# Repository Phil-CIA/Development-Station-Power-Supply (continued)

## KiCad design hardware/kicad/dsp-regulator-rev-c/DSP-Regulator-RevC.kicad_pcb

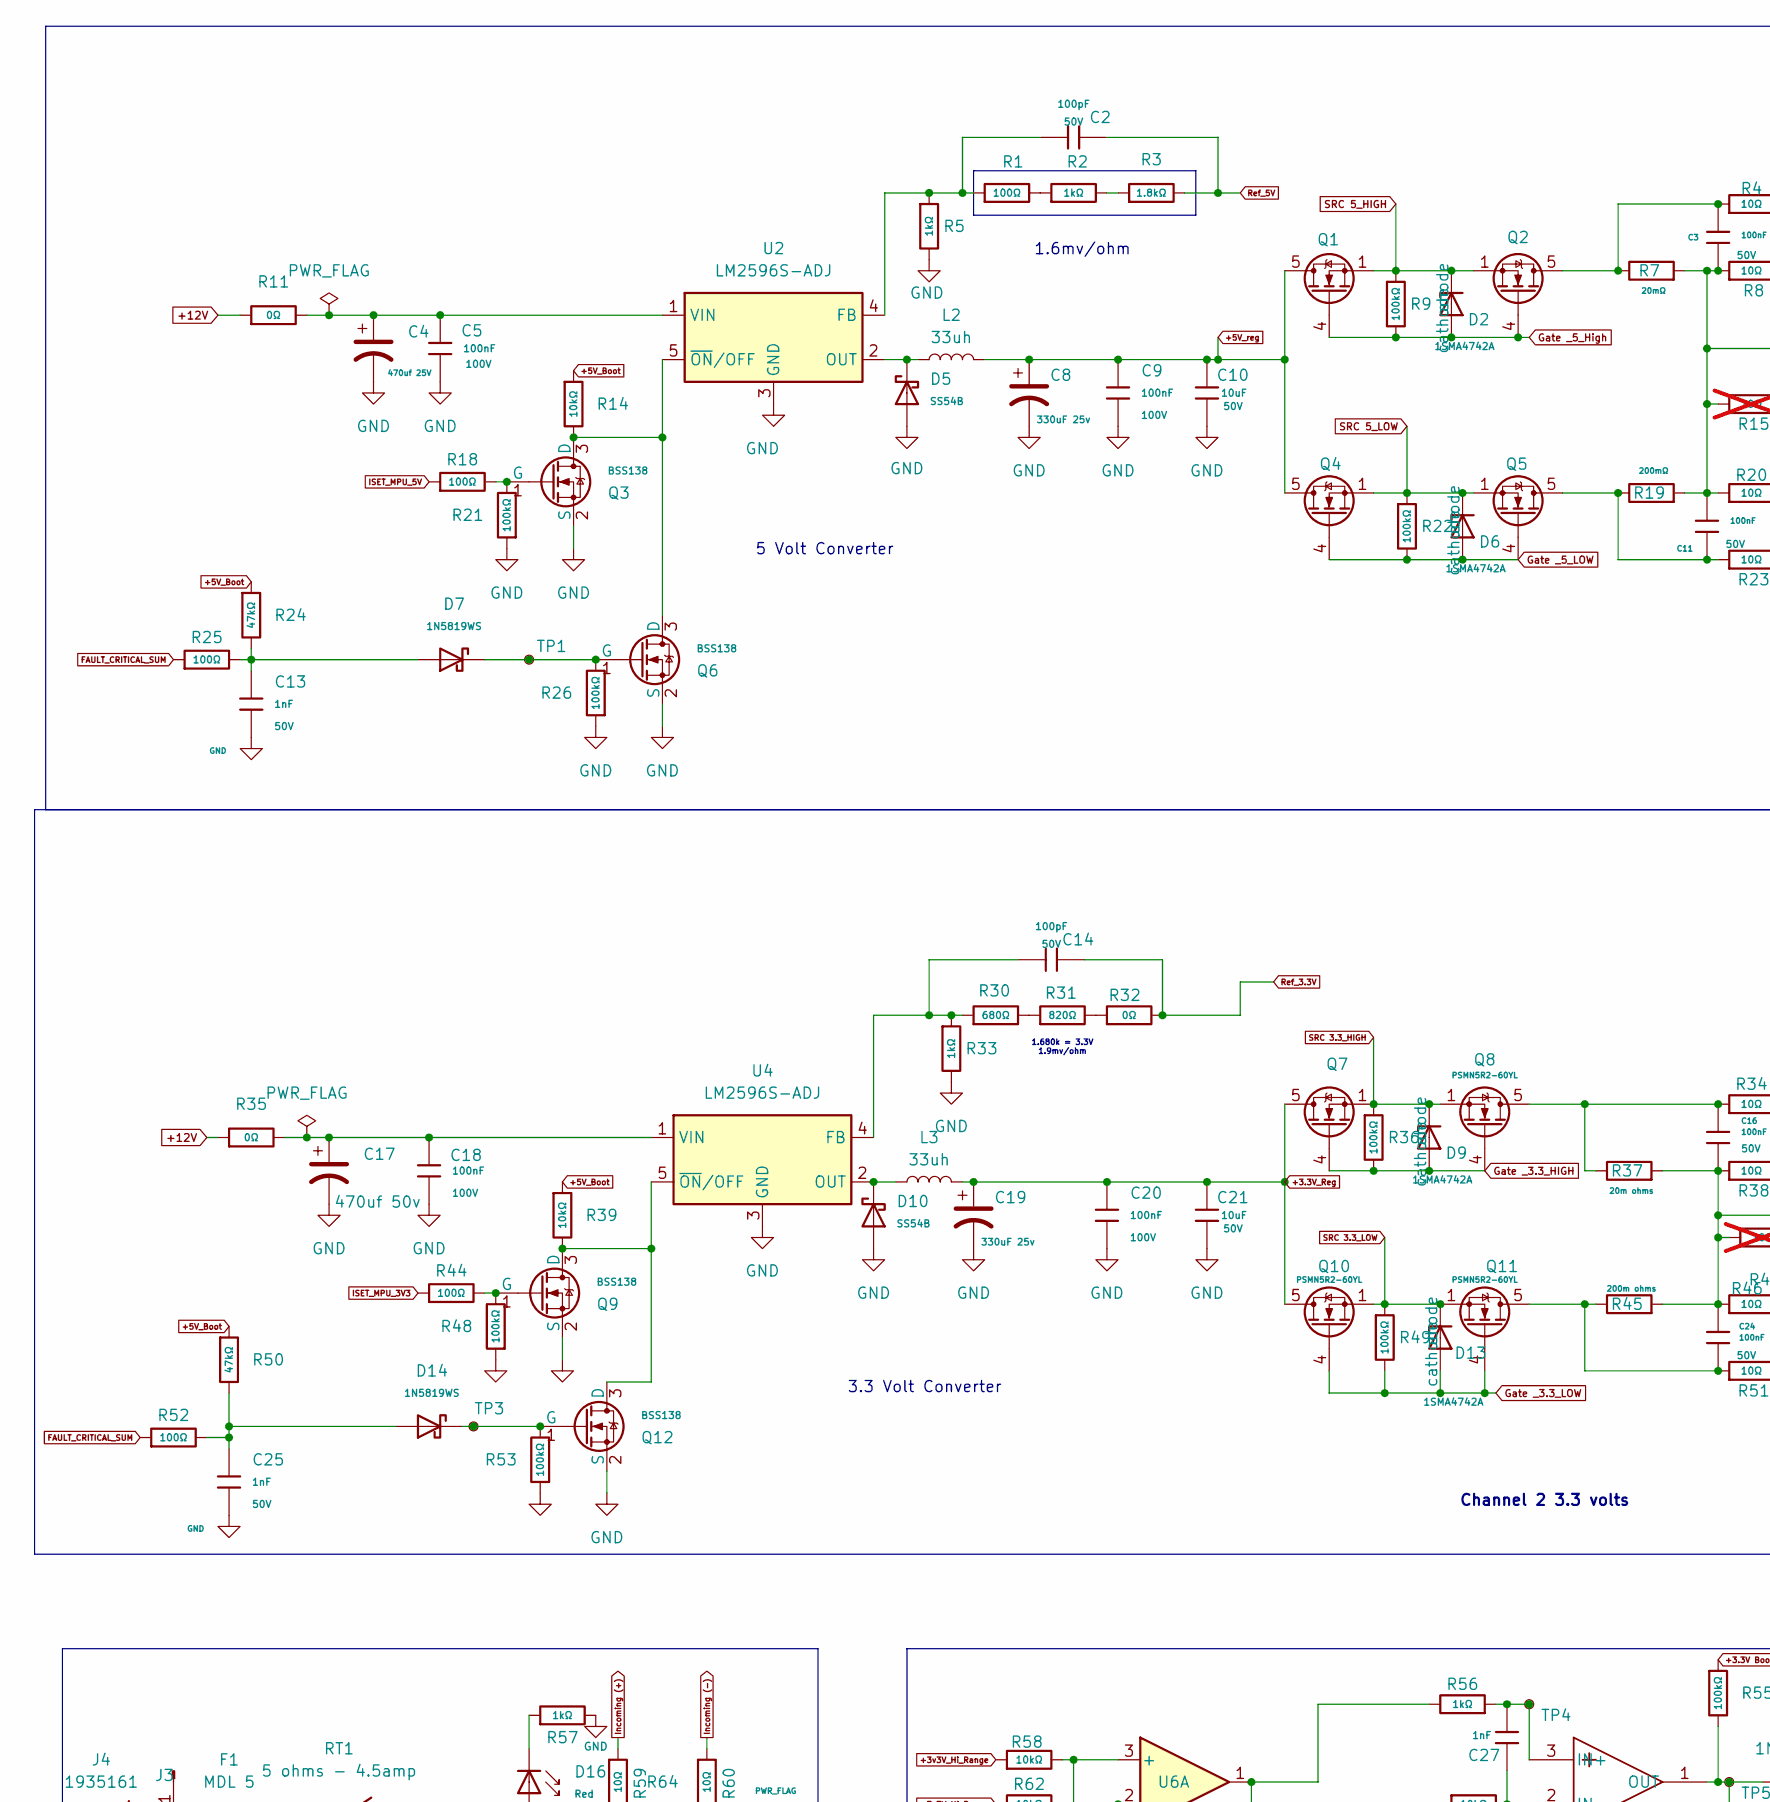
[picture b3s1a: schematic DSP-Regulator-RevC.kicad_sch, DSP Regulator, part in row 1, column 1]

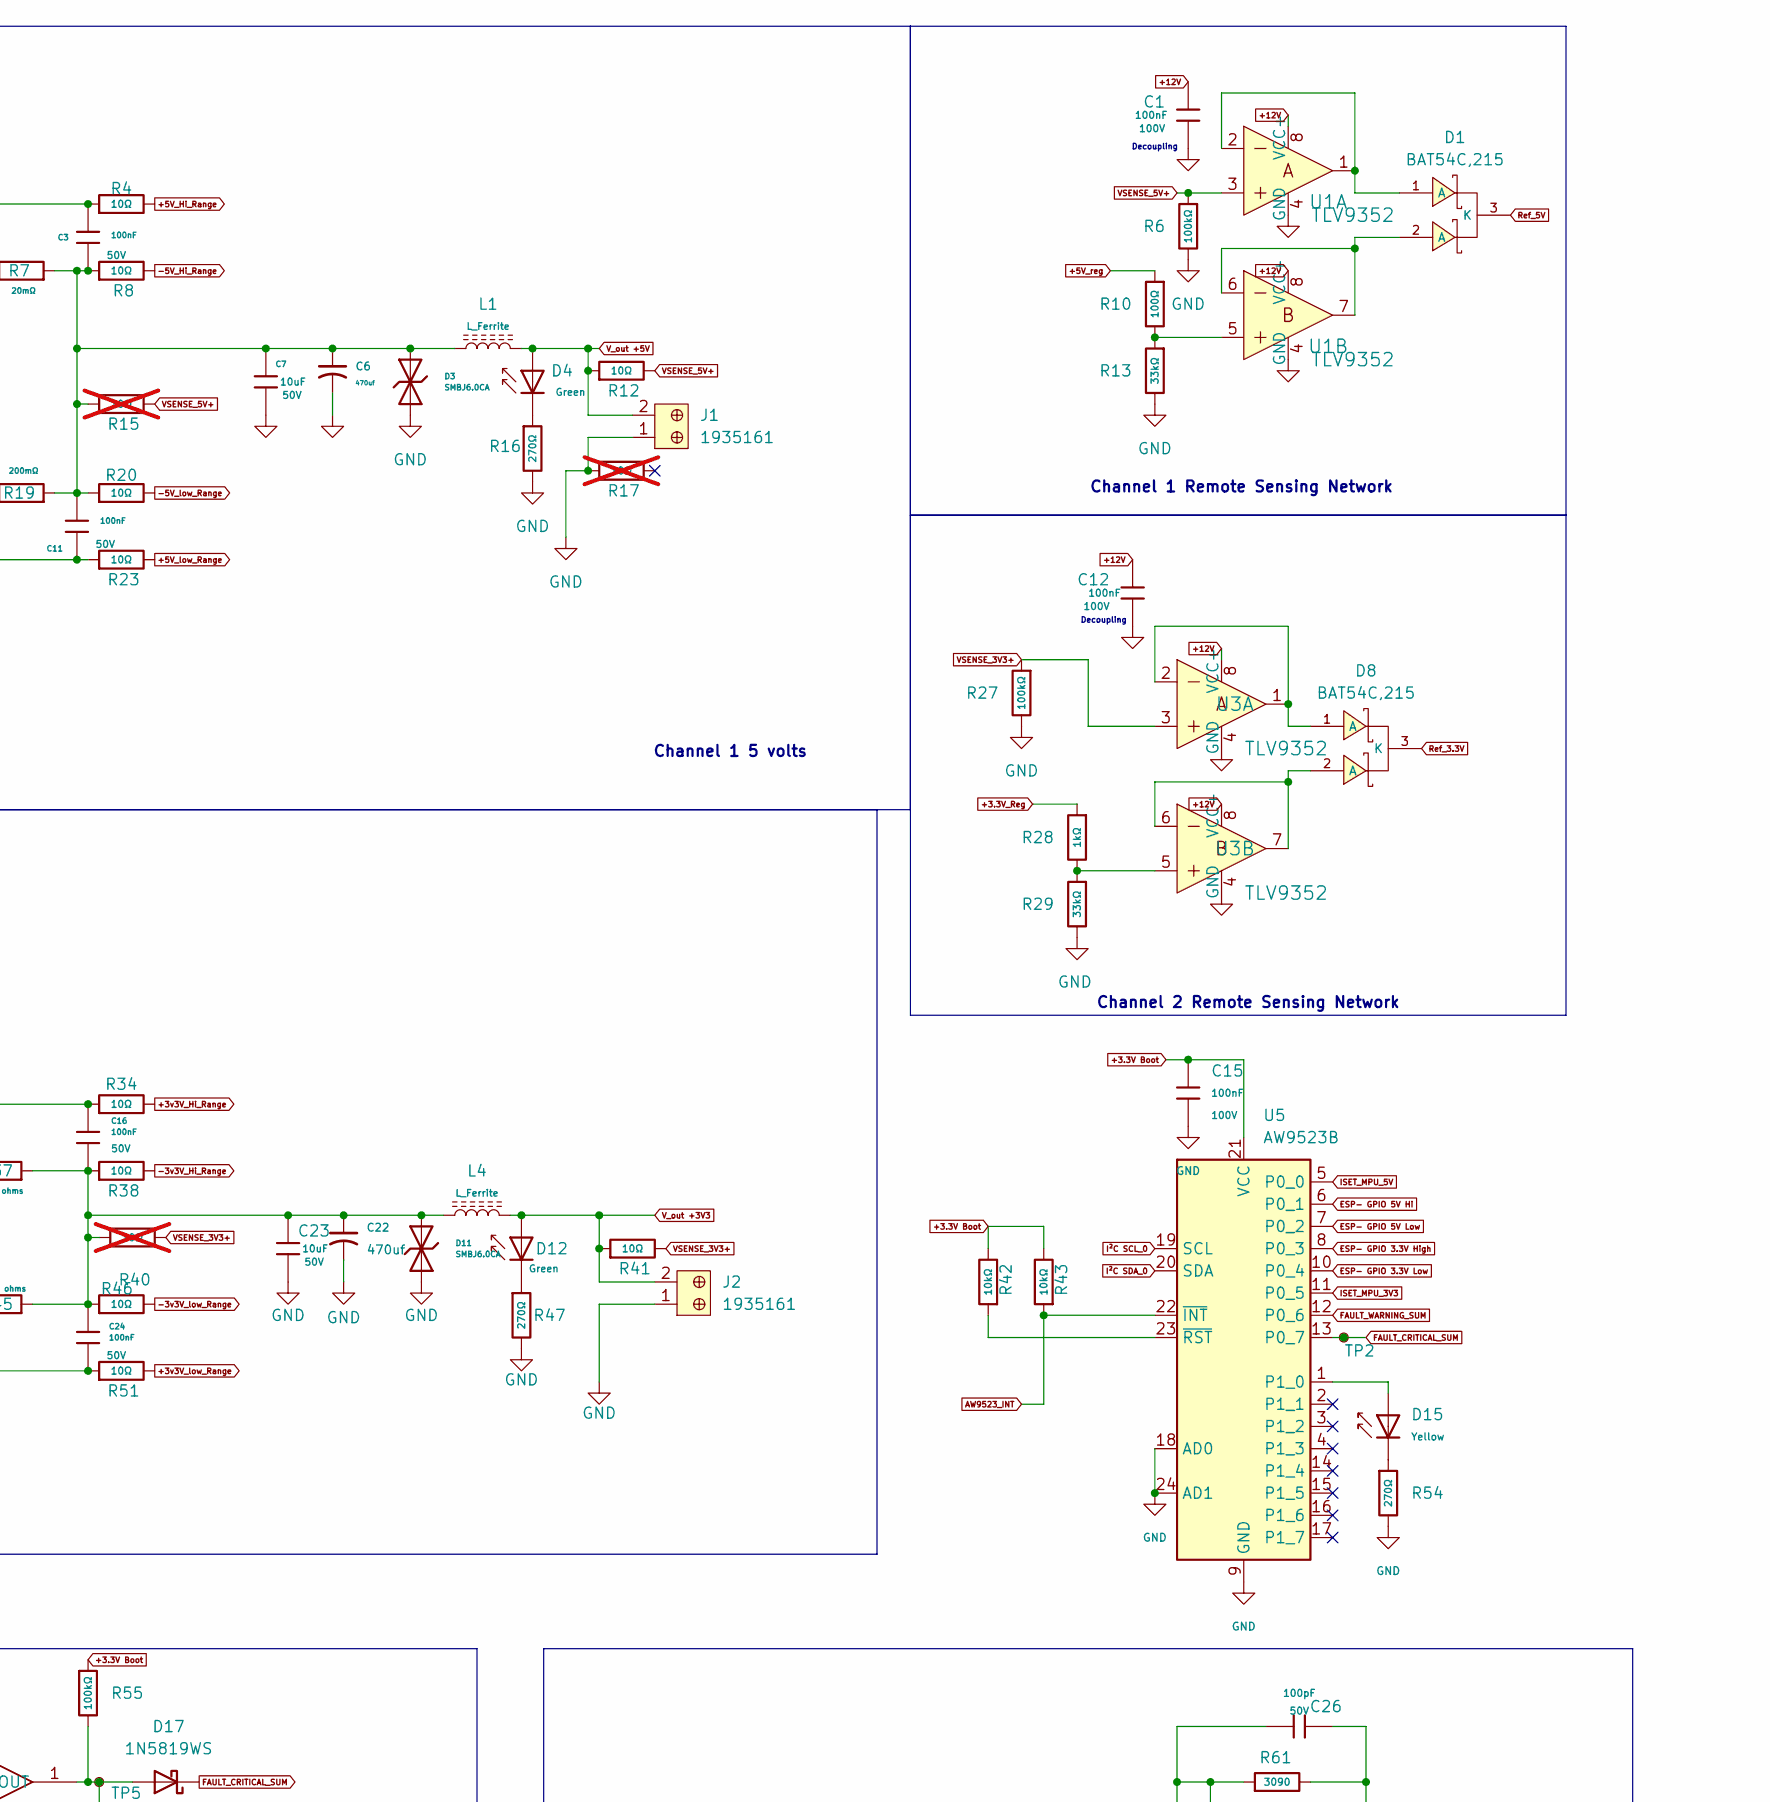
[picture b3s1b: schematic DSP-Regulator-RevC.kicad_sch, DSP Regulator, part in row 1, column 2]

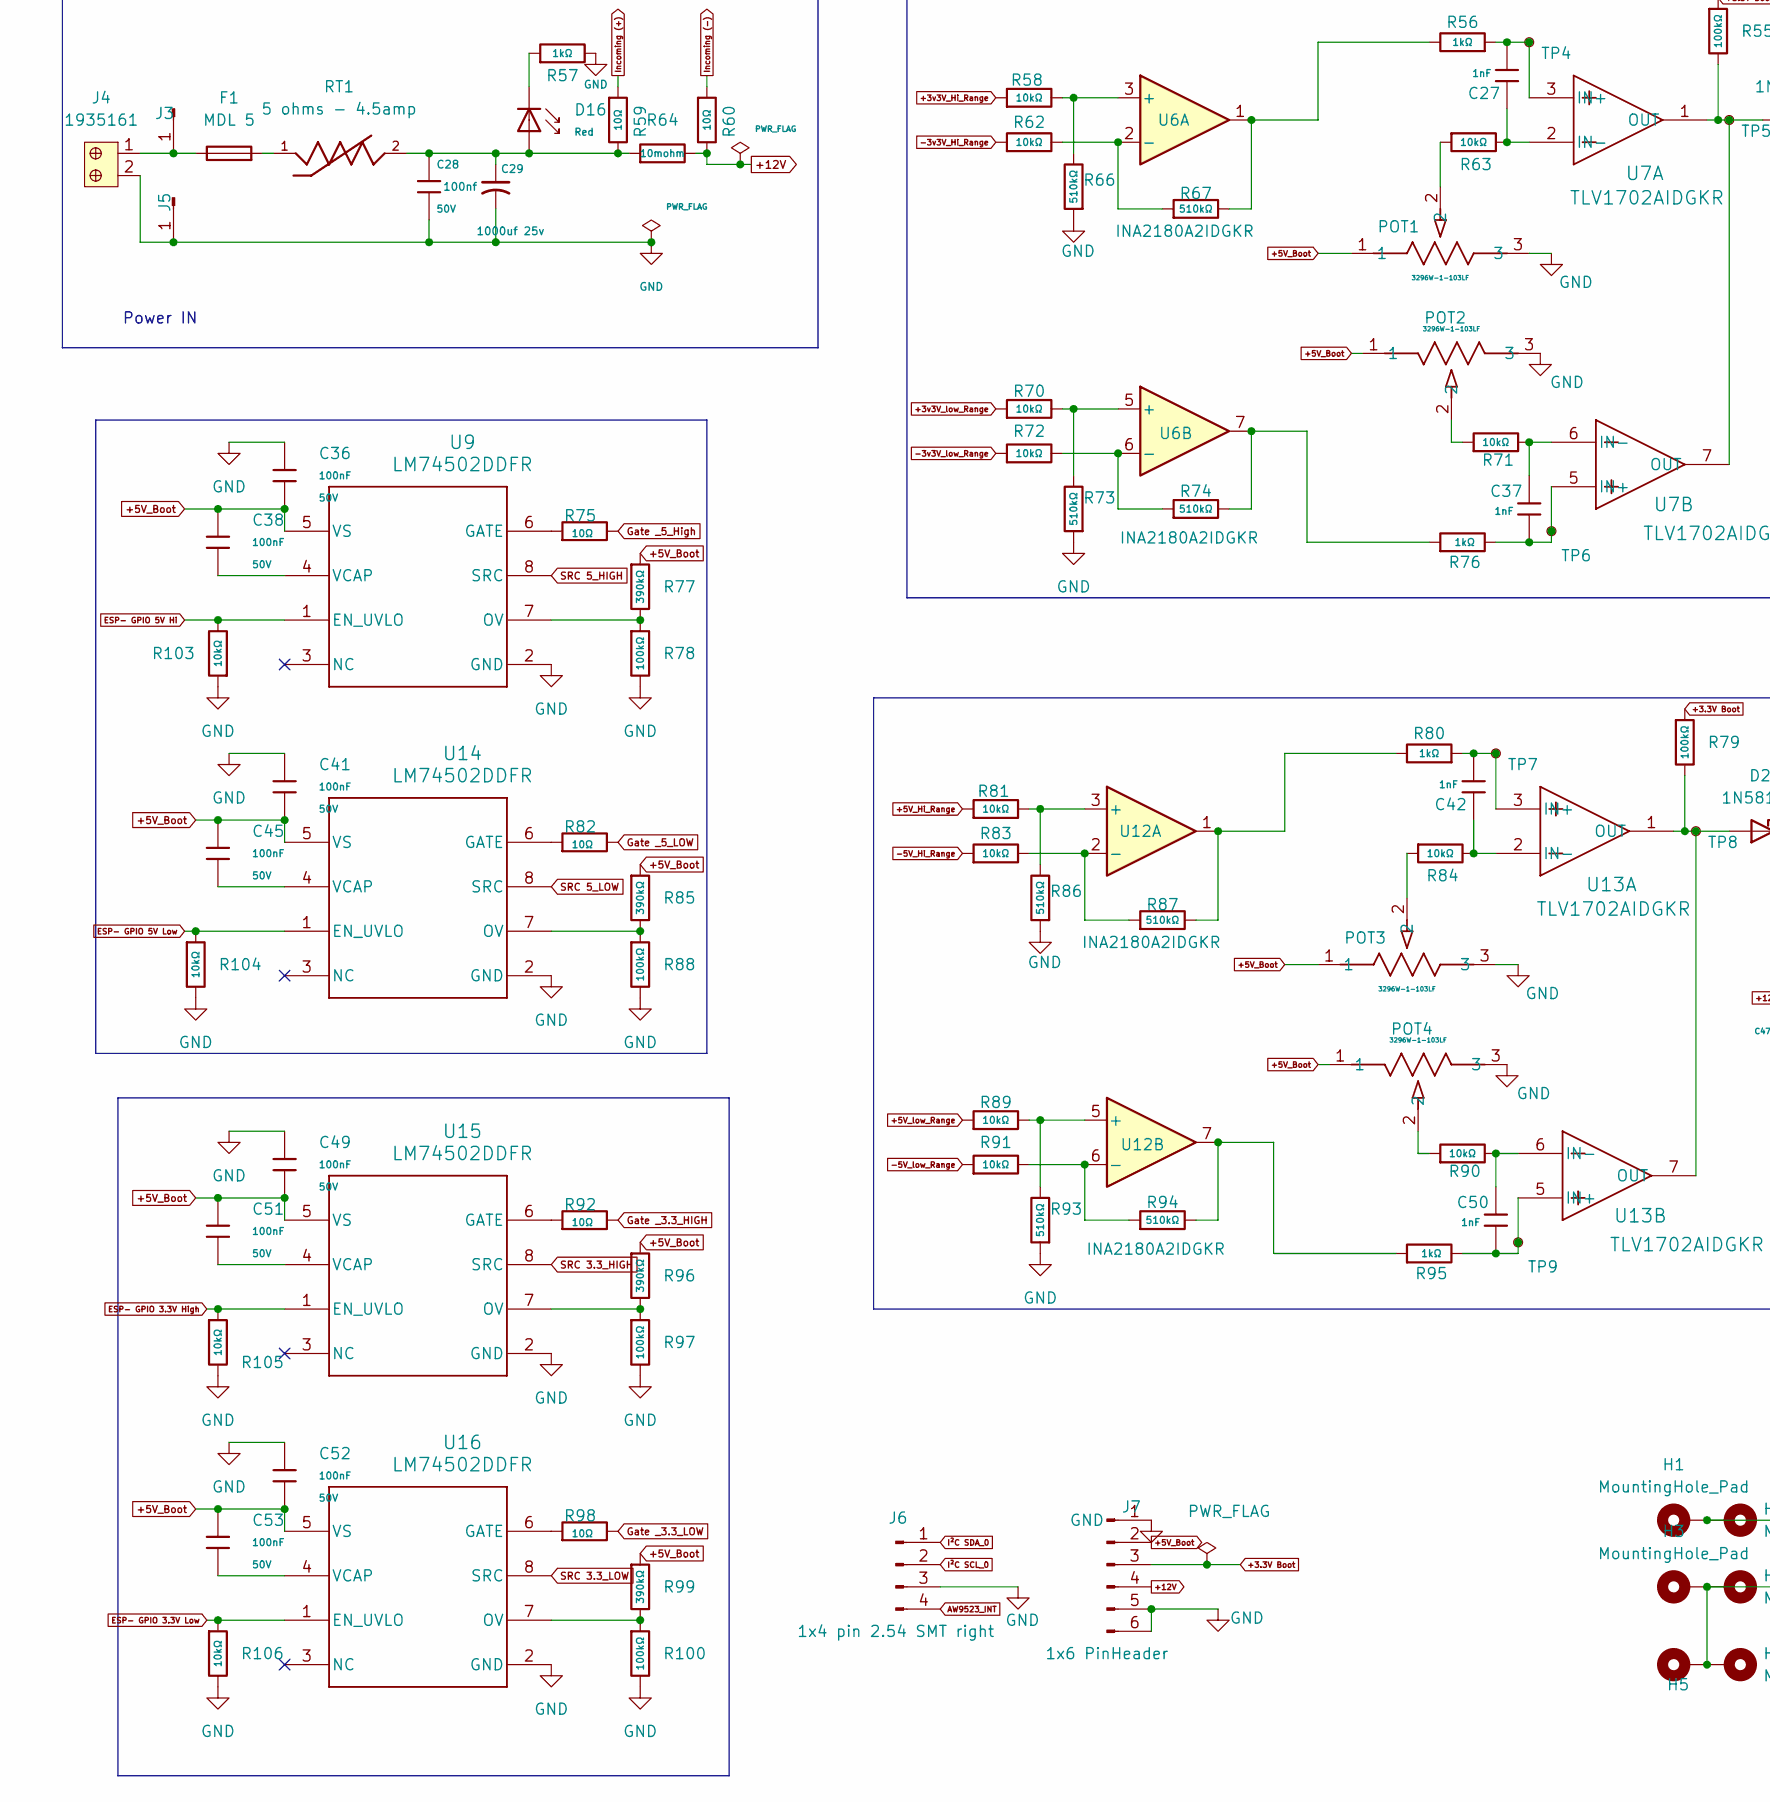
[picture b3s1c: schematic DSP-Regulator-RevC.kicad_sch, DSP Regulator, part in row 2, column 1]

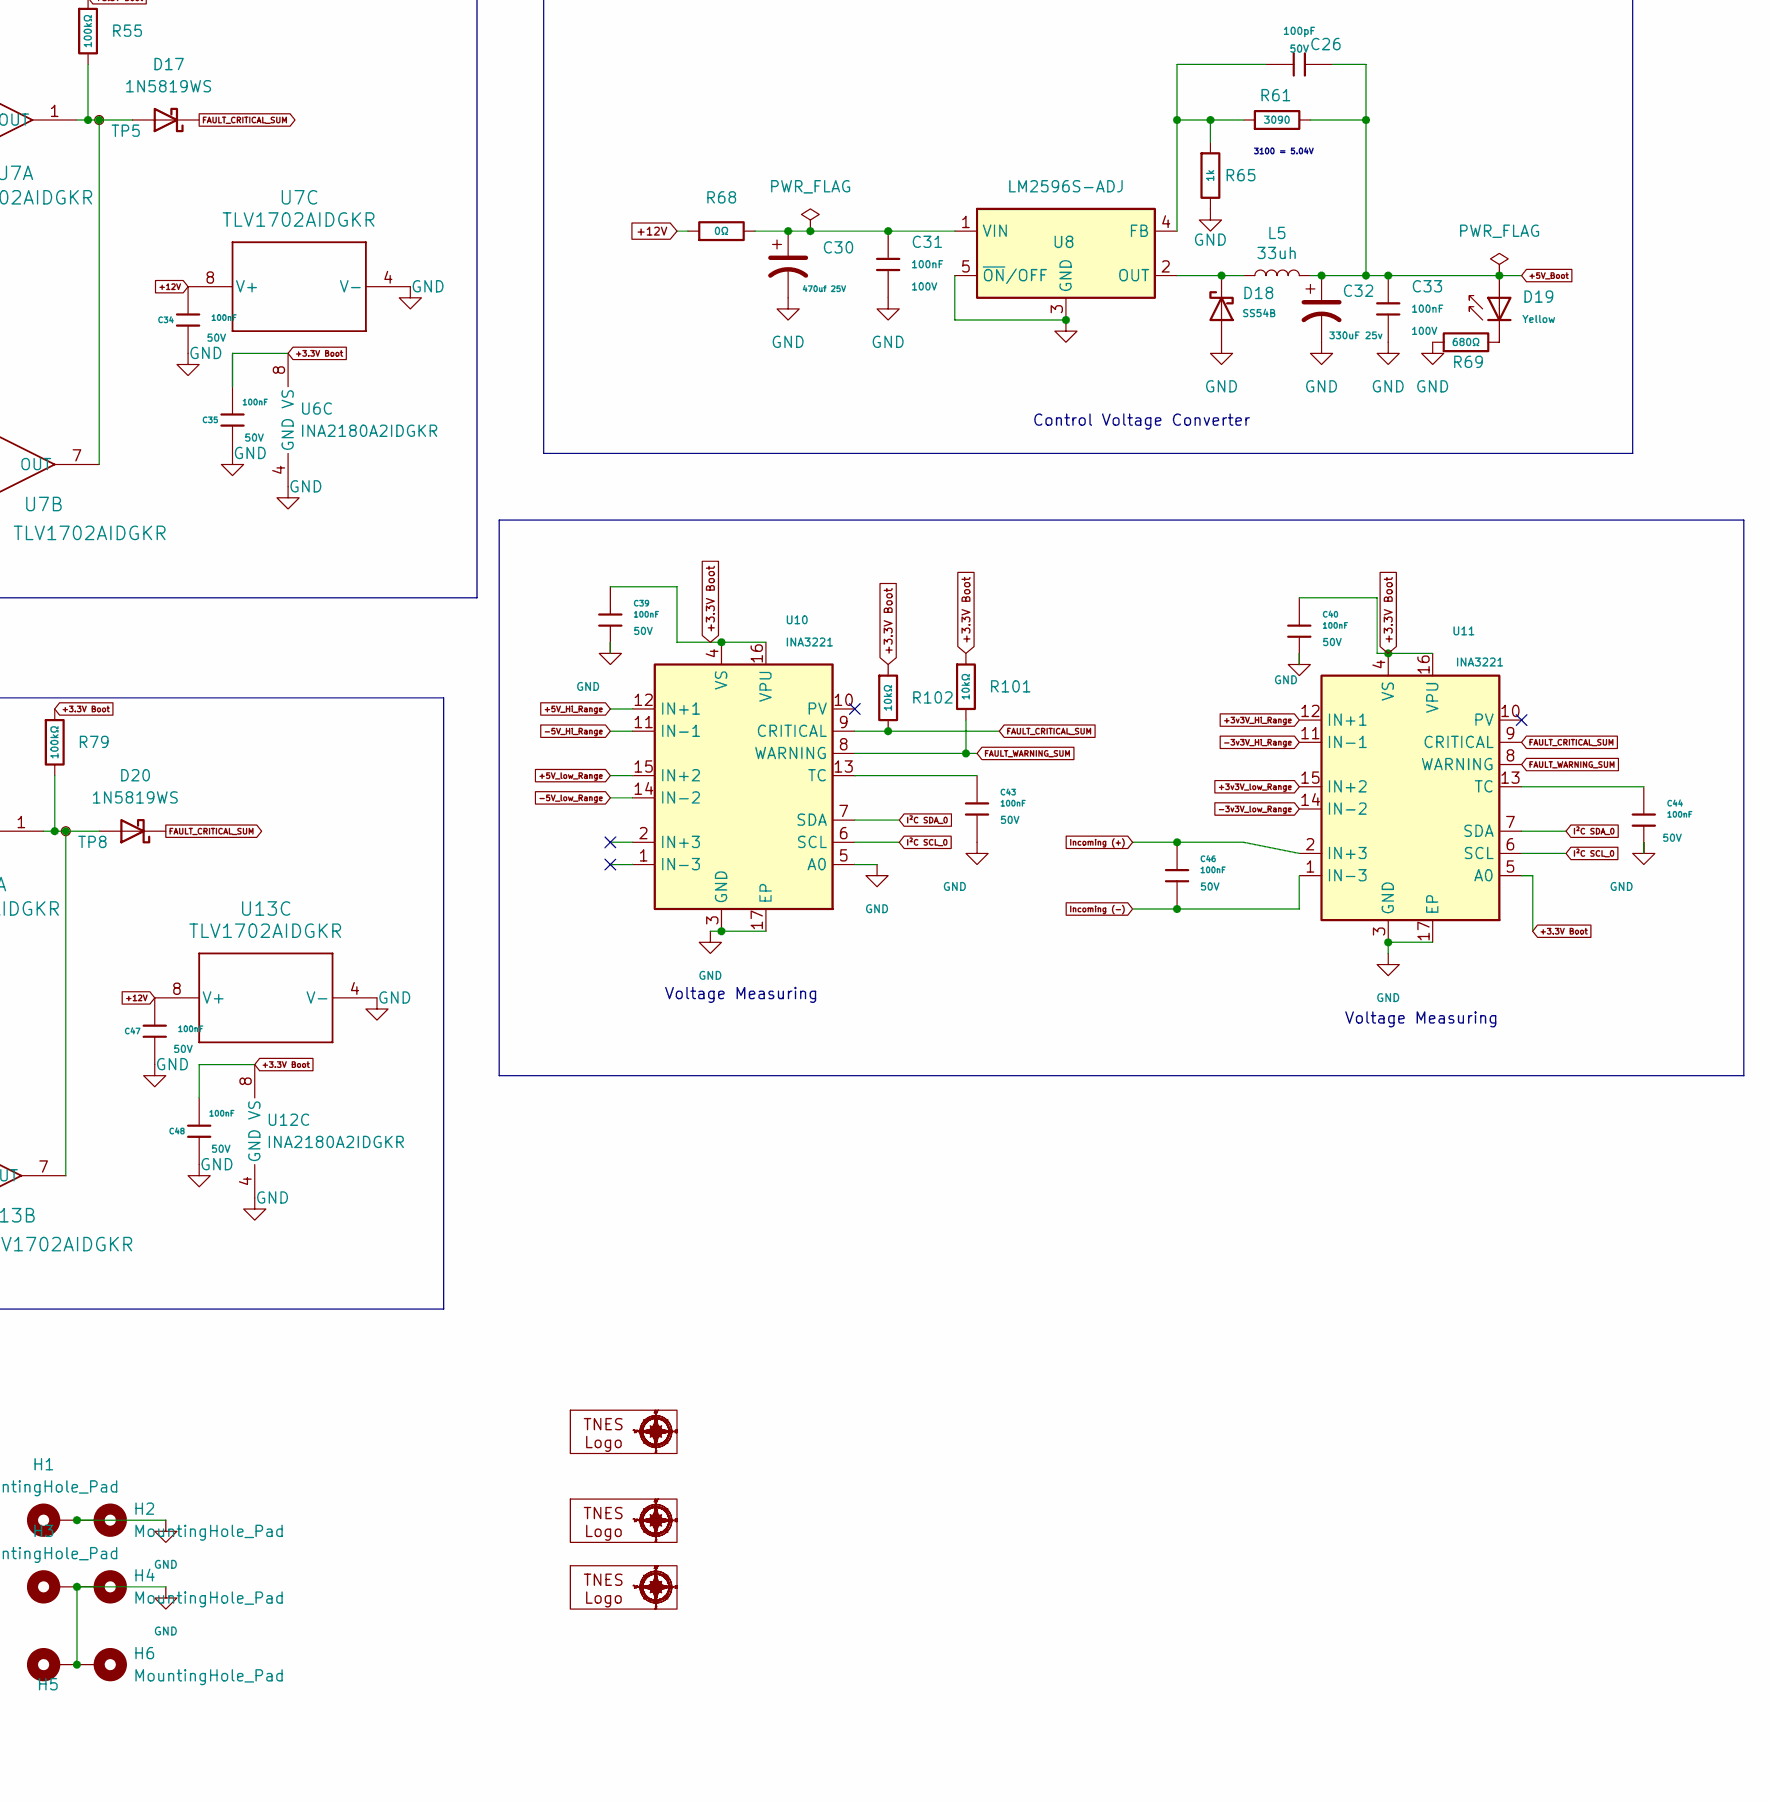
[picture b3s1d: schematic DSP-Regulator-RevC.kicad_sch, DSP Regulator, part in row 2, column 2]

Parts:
5mm1: 5mm LOGO
10mm1, 10mm2: 10mm LOGO
C1, C9, C12, C15, C31, C33: 100nF; C_0805; Voltage Rated 100V; Tolerance ±10%; Part CL21B104KCFNNNE; LCSC C28233
C2, C14: 100pF; C_0805_2012Metric; Voltage Rated 50V; Tolerance ±5%; Part CL21C101JBANNNC; LCSC C1790
C3, C11, C16, C24, C34, C35, C36, C39, C40, C41, C43, C44, C45, C46, C47, C48, C49, C51, C52, C53: 100nF; C_0805; Voltage Rated 50V; Tolerance ±10%; Part CC0805KRX7R9BB104; LCSC C49678
C4, C30: 470uf 25V; CP_Elec_10x10.5; Voltage Class 25; LCSC C48615124
C5, C18, C20: 100nF; C_0805_2012Metric; Voltage Rated 100V; Tolerance ±10%; Part CL21B104KCFNNNE; LCSC C28233
C6, C22: 470uf; CP_Elec_10x10; Part JVE25V470M10X10; LCSC C48615124
C7, C10, C21, C23: 10uF; C_0805; Voltage Rated 50V; Tolerance ±10%; Part GRM21BR61H106KE43L; LCSC C440198
C8, C19, C32: 330uF 25v; CP_Elec_10x10.5; LCSC C72510
C13, C25: 1nF; C_0805_2012Metric; Voltage Rated 50V; Tolerance ±10%; Part CL21B102KBCNNNC; LCSC C46653
C17: 470uf 50v; CP_Elec_10x10.5; Voltage Class 50; LCSC C34642
C26: 100pF; C_0805; Voltage Rated 50V; Tolerance ±5%; Part CL21C101JBANNNC; LCSC C1790
C27, C37, C42, C50: 1nF; C_0805; Voltage Rated 50V; Tolerance ±10%; Part CL21B102KBCNNNC; LCSC C46653
C28: 100nf; C_0805_2012Metric; Voltage Rated 50V; Tolerance ±10%; Part CL21B104KCFNNNE; LCSC C28233
C29: 1000uf 25v; C_Elec_10x10.2; Part EEEFT1E102UP; LCSC C401766
C38: 100nF; C_0805_2012Metric; Voltage Rated 50V; Tolerance ±10%; Part CC0805KRX7R9BB104; LCSC C49678
D1, D8: BAT54C,215; SOT-23-3_L2.9-W1.6-P1.90-LS2.8-BR; Reverse Voltage (Vr) 30V; Forward Voltage (Vf@If) 800mV@100mA; Part BAT54C,215; LCSC C37704
D2, D6, D9, D13: 1SMA4742A; D_DO-214AC(SMA); Part 1SMA4742A; LCSC C19077480
D3, D11: SMBJ6.0CA; D_SMB; Clamping Voltage 10.3V; Voltage - Breakdown 6.67V; PARTREV F2102; LCSC C19077561
D4, D12: Green; D_0805; Part KT-0805G; LCSC C2297
D5, D10, D18: SS54B; D_SMB; Voltage - Forward(Vf@If) 550mV@5.0A; Voltage - DC Reverse(Vr) 40V; Part SS54B; LCSC C18199181
D7, D14: 1N5819WS; D_SOD-323; Forward Voltage (Vf@If) 600mV@1A; Reverse Voltage (Vr) 40V; Part 1N5819WS; LCSC C191023
D15, D19: Yellow; D_0805; Part KT-0805Y; LCSC C2296
D16: Red; D_0805; Forward Voltage (VF) 1.6V~2.6V; Part NCD0805R1; LCSC C84256
D17, D20: 1N5819WS; D_SOD-323; LCSC C191023
F1: MDL 5; Fuseholder_Clip-6.3x32mm_Littelfuse_102_Inline_P34.21x7.62m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
H1, H2, H3, H4, H5, H6: MountingHole_Pad; MountingHole_3.2mm_M3_Pad_Via
J1, J2, J4: 1935161; Terminal_Block_D1.3mm_P5mm; MPN 1935161; Digi-Key_PN 277-1667-ND
J3, J5: Wire con; SolderWire-1sqmm_1x01_D1.4mm_OD2.7mm
J6: 1x4 pin 2.54 SMT right; PinHeader_1x04_P2.54mm_Vertical_SMD_Pin1Right; LCSC C41417361
J7: 1x6 PinHeader; PinHeader_1x06_P2.54mm_Vertical_SMD_Pin1Right; LCSC C41417363
L1, L4: L_Ferrite; L_1206_3216Metric; LCSC C85841
L2, L3, L5: 33uh; L_Sunlord_MWSA1003S; LCSC C149598
POT1, POT2, POT3, POT4: 3296W-1-103LF; Potentiometer_Bourns_3296W_Vertical; MPN TC33X-2-103E; Digi-Key_PN TC33X-103ETR-ND
Q1, Q2, Q4, Q5, Q7, Q8, Q10, Q11: PSMN5R2-60YL; LFPAK56; Part PSMN5R2-60YLX; LCSC TBD
Q3, Q6, Q9, Q12: BSS138; Q_SOT-23; Part BSS138; LCSC C7420339
R1, R10, R18, R25, R44, R52: 100Ω; R_0805; Overload Voltage (Max) 150V; Tolerance ±1%; Part 0805W8F1000T5E; LCSC C17408
R2, R5, R28, R33, R56, R57, R76, R80, R95: 1kΩ; R_0805; Overload Voltage (Max) 150V; Tolerance ±1%; Part 0805W8F1001T5E; LCSC C17513
R3: 1.8kΩ; R_0805; Overload Voltage (Max) 150V; Tolerance ±1%; Part 0805W8F1801T5E; LCSC C17398
R4, R8, R12, R20, R23, R34, R38, R41, R46, R51, R59, R60, R75, R82, R92, R98: 10Ω; R_0805; Overload Voltage (Max) 150V; Tolerance ±1%; Part 0805W8F100JT5E; LCSC C17415
R6, R9, R21, R22, R26, R27, R36, R48, R49, R53, R55, R78, R79, R88, R97, R100: 100kΩ; R_0805; Overload Voltage (Max) 150V; Tolerance ±1%; Part 0805W8F1003T5E; LCSC C149504
R7: 20mΩ; R_2512_6332Metric; LCSC C49164694
R11, R35, R68: 0Ω; R_1206; Overload Voltage (Max) 200V; Tolerance ±1%; Part 1206W4F0000T5E; LCSC C17888
R13, R29: 33kΩ; R_0805; Overload Voltage (Max) 150V; Tolerance ±1%; Part 0805W8F3302T5E; LCSC C17633
R14, R39, R42, R43, R58, R62, R63, R70, R71, R72, R81, R83, R84, R89, R90, R91, R101, R102, R103, R104, R105, R106: 10kΩ; R_0805; Overload Voltage (Max) 150V; Tolerance ±1%; Part 0805W8F1002T5E; LCSC C17414
R15, R17, R40: 10Ω; R_0805; Overload Voltage (Max) 150V; Tolerance ±1%; Part 0805W8F100JT5E; LCSC C17415; not fitted
R16, R47, R54: 270Ω; R_0805; Overload Voltage (Max) 150V; Tolerance ±1%; Part 0805W8F2700T5E; LCSC C17590
R19: 200mΩ; R_2512_6332Metric; LCSC C7420022
R24, R50: 47kΩ; R_0805; Overload Voltage (Max) 150V; Tolerance ±1%; Part 0805W8F4702T5E; LCSC C17713
R30, R69: 680Ω; R_0805; Overload Voltage (Max) 150V; Tolerance ±1%; Part 0805W8F6800T5E; LCSC C17798
R31: 820Ω; R_0805; Overload Voltage (Max) 150V; Tolerance ±1%; Part 0805W8F8200T5E; LCSC C17837
R32: 0Ω; R_0805; Overload Voltage (Max) 150V; Tolerance ±1%; Part 0805W8F0000T5E; LCSC C17477
R37: 20m ohms; R_2512_6332Metric; LCSC C49164694
R45: 200m ohms; R_2512_6332Metric; LCSC C7420022
R61: 3090; R_0805; LCSC C5121539
R64: 10mohm; R_0805; Overload Voltage (Max) 150V; Tolerance ±1%; Part 0805W8F0000T5E; LCSC C17477
R65: 1k; R_0805; Overload Voltage (Max) 150V; Tolerance ±1%; Part 0805W8F1001T5E; LCSC C17513
R66, R67, R73, R74, R86, R87, R93, R94: 510kΩ; R_0805; Overload Voltage (Max) 150V; Tolerance ±1%; Part 0805W8F5103T5E; LCSC C17733
R77, R85, R96, R99: 390kΩ; R_0805; Overload Voltage (Max) 150V; Tolerance ±1%; Part 0805W8F3903T5E; LCSC C17656
RT1: 5 ohms - 4.5amp; RV_Disc_D7mm_W4.5mm_P5mm; PARTREV 8/1/2022
TP1, TP2, TP3: TestPoint_Small; PinHeader_1x01_P2.54mm_Vertical
TP4, TP5, TP6, TP7, TP8, TP9: TestPoint_Small; PinHeader_1x01_P1.00mm_Vertical
U1, U3: TLV9352; SOIC-8_W3.9mm; MPN LMV358IDR; Digi-Key_PN 296-9571-1-ND
U2, U4, U8: LM2596S-ADJ; TO-263-5_TabPin3; LCSC C347423
U5: AW9523B; QFN-24-1EP_4x4mm_P0.5mm_EP2.7x2.7mm; LCSC C148077
U6, U12: INA2180A2IDGKR; VSSOP-8_3x3mm_P0.65mm; LCSC C2058508
U7, U13: TLV1702AIDGKR; Texas_S-PDSO-G8_3x3mm_P0.65mm; LCSC C2870937
U9, U14, U15, U16: LM74502DDFR; TSOT-23-8; LCSC C3236215
U10, U11: INA3221; Texas_RGV0016A_VQFN-16-1EP_4x4mm_P0.65mm_EP2.1x2.1mm; LCSC C181255

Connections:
+3.3V Boot: C15.1, C35.1, C39.1, C40.1, C48.1, J7.3, R42.2, R43.2, R55.1, R79.1, R101.1, R102.1, U5.21 (VCC), U6.8 (VS), U10.4 (VS), U10.16 (VPU), U11.4 (VS), U11.5 (A0), U11.16 (VPU), U12.8 (VS)
+3.3V_Reg: C19.1, C20.1, C21.1, L3.2, Q7.5 (D), Q10.5 (D), R28.1
+3v3V_Hi_Range: R34.2, R58.1, U11.12 (IN+1)
+3v3V_low_Range: R51.2, R70.1, U11.15 (IN+2)
+5V_Boot: C26.1, C32.1, C33.1, C36.2, C38.1, C41.2, C45.1, C49.2, C51.1, C52.2, C53.1, D19.2, J7.2, L5.2, POT1.1, POT2.1, POT3.1, POT4.1, R14.1, R24.1, R39.1, R50.1, R61.2, R77.1, R85.1, R96.1, R99.1, U9.5 (VS), U14.5 (VS), U15.5 (VS), U16.5 (VS)
+5V_Hi_Range: R4.2, R81.1, U10.12 (IN+1)
+5V_low_Range: R23.2, R89.1, U10.15 (IN+2)
+5V_reg: C8.1, C9.1, C10.1, L2.2, Q1.5 (D), Q4.5 (D), R10.1
+12V: C1.1, C12.1, C34.1, C47.1, J7.4, R11.1, R35.1, R60.2, R64.2, R68.1, U1.8 (VCC+), U3.8 (VCC+), U7.8 (V+), U13.8 (V+)
-3v3V_Hi_Range: R38.2, R62.1, U11.11 (IN-1)
-3v3V_low_Range: R46.2, R72.1, U11.14 (IN-2)
-5V_Hi_Range: R8.2, R83.1, U10.11 (IN-1)
-5V_low_Range: R20.2, R91.1, U10.14 (IN-2)
AW9523_INT: J6.4, R43.1, U5.22 (~INT)
ESP- GPIO 3.3V High: R105.1, U5.8 (P0_3), U15.1 (EN_UVLO)
ESP- GPIO 3.3V Low: R106.1, U5.10 (P0_4), U16.1 (EN_UVLO)
ESP- GPIO 5V Hi: R103.2, U5.6 (P0_1), U9.1 (EN_UVLO)
ESP- GPIO 5V Low: R104.1, U5.7 (P0_2), U14.1 (EN_UVLO)
FAULT_CRITICAL_SUM: D17.1 (K), D20.1 (K), R25.1, R52.1, R102.2, TP2.1 (1_1), U5.13 (P0_7), U10.9 (CRITICAL), U11.9 (CRITICAL)
FAULT_WARNING_SUM: R101.2, U5.12 (P0_6), U10.8 (WARNING), U11.8 (WARNING)
GND: C1.2, C4.2, C5.2, C6.2, C7.2, C8.2, C9.2, C10.2, C12.2, C13.2, C15.2, C17.2, C18.2, C19.2, C20.2, C21.2, C22.2, C23.2, C25.2, C28.2, C29.2, C30.2, C31.2, C32.2, C33.2, C34.2, C35.2, C36.1, C39.2, C40.2, C41.1, C43.2, C44.2, C47.2, C48.2, C49.1, C52.1, D3.1, D5.2, D10.2, D11.1, D18.2, H1.1 (1_1), H2.1 (1_1), H3.1 (1_1), H4.1 (1_1), H5.1 (1_1), H6.1 (1_1), J1.1, J2.1, J4.2, J5.1 (Pin_1_1), J6.3, J7.1, J7.5, J7.6, POT1.3, POT2.3, POT3.3, POT4.3, Q3.2 (S), Q6.2 (S), Q9.2 (S), Q12.2 (S), R5.2, R6.2, R13.2, R16.2, R17.1, R21.1, R26.1, R27.2, R29.2, R33.2, R47.2, R48.1, R53.1, R54.2, R57.2, R65.2, R66.1, R69.1, R73.1, R78.2, R86.1, R88.2, R93.1, R97.2, R100.2, R103.1, R104.2, R105.2, R106.2, U1.4 (GND), U2.3 (GND), U3.4 (GND), U4.3 (GND), U5.9 (GND), U5.18 (AD0), U5.24 (AD1), U5.25 (GND), U6.4 (GND), U7.4 (V-), U8.3 (GND), U8.5 (~ON/OFF), U9.2 (GND), U10.3 (GND), U10.5 (A0), U10.17 (EP), U11.3 (GND), U11.17 (EP), U12.4 (GND), U13.4 (V-), U14.2 (GND), U15.2 (GND), U16.2 (GND)
Gate _3.3_HIGH: D9.2 (cathode), Q7.4 (G), Q8.4 (G), R36.2, R92.2
Gate _3.3_LOW: D13.2 (cathode), Q10.4 (G), Q11.4 (G), R49.2, R98.2
Gate _5_High: D2.2 (cathode), Q1.4 (G), Q2.4 (G), R9.2, R75.2
Gate _5_LOW: D6.2 (cathode), Q4.4 (G), Q5.4 (G), R22.2, R82.2
ISET_MPU_3V3: R44.1, U5.11 (P0_5)
ISET_MPU_5V: R18.1, U5.5 (P0_0)
Incoming (+): C46.1, R59.1, U11.2 (IN+3)
Incoming (-): C46.2, R60.1, U11.1 (IN-3)
I²C SCL_0: J6.2, U5.19 (SCL), U10.6 (SCL), U11.6 (SCL)
I²C SDA_0: J6.1, U5.20 (SDA), U10.7 (SDA), U11.7 (SDA)
unnamed: C3.2, C6.1, C7.1, C11.1, D3.2, L1.1, R7.2, R8.1, R15.1, R19.2, R20.1
unnamed: C13.1, D7.2, R24.2, R25.2
unnamed: C16.2, C22.1, C23.1, C24.1, D11.2, L4.1, R37.2, R38.1, R40.1, R45.2, R46.1
unnamed: C25.1, D14.2, R50.2, R52.2
unnamed: C28.1, C29.1, D16.2, R59.2, R64.1, RT1.2
unnamed: D1.1 (A), U1.1, U1.2
unnamed: D1.2 (A), U1.6, U1.7
unnamed: D4.1, R16.1
unnamed: D8.1 (A), U3.1, U3.2
unnamed: D8.2 (A), U3.6, U3.7
unnamed: D12.1, R47.1
unnamed: D15.1, R54.1
unnamed: D16.1, R57.1
unnamed: D17.2 (A), R55.2, TP5.1 (1_1), U7.1 (OUT), U7.7 (OUT)
unnamed: D19.1, R69.2
unnamed: D20.2 (A), R79.2, TP8.1 (1_1), U13.1 (OUT), U13.7 (OUT)
unnamed: F1.2, RT1.1
unnamed: F1.1, J3.1 (Pin_1_1), J4.1
unnamed: POT1.2, R63.1
unnamed: POT2.2, R71.1
unnamed: POT3.2, R84.1
unnamed: POT4.2, R90.1
unnamed: C3.1, Q2.5 (D), R4.1, R7.1
unnamed: Q3.3 (D), Q6.3 (D), R14.2, U2.5 (~ON/OFF)
unnamed: Q3.1 (G), R18.2, R21.2
unnamed: C11.2, Q5.5 (D), R19.1, R23.1
unnamed: D7.1, Q6.1 (G), R26.2, TP1.1 (1_1)
unnamed: C16.1, Q8.5 (D), R34.1, R37.1
unnamed: Q9.1 (G), R44.2, R48.2
unnamed: C24.2, Q11.5 (D), R45.1, R51.1
unnamed: Q9.3 (D), Q12.3 (D), R39.2, U4.5 (~ON/OFF)
unnamed: D14.1, Q12.1 (G), R53.2, TP3.1 (1_1)
unnamed: R1.2, R2.1
unnamed: R2.2, R3.1
unnamed: R10.2, R13.1, U1.5
unnamed: R28.2, R29.1, U3.5
unnamed: R30.2, R31.1
unnamed: R31.2, R32.1
unnamed: R56.2, R67.2, U6.1
unnamed: R74.2, R76.1, U6.7
unnamed: R80.2, R87.2, U12.1
unnamed: R94.2, R95.1, U12.7
unnamed: C2.2, R1.1, R5.1, U2.4 (FB)
unnamed: D5.1, L2.1, U2.2 (OUT)
unnamed: C4.1, C5.1, R11.2, U2.1 (VIN)
unnamed: C14.2, R30.1, R33.1, U4.4 (FB)
unnamed: D10.1, L3.1, U4.2 (OUT)
unnamed: C17.1, C18.1, R35.2, U4.1 (VIN)
unnamed: D15.2, U5.1 (P1_0)
unnamed: R42.1, U5.23 (~RST)
unnamed: R58.2, R66.2, U6.3 (+)
unnamed: R62.2, R67.1, U6.2 (-)
unnamed: R70.2, R73.2, U6.5 (+)
unnamed: R72.2, R74.1, U6.6 (-)
unnamed: C27.2, R56.1, TP4.1 (1_1), U7.3 (IN+)
unnamed: C27.1, R63.2, U7.2 (IN-)
unnamed: C37.2, R76.2, TP6.1 (1_1), U7.5 (IN+)
unnamed: C37.1, R71.2, U7.6 (IN-)
unnamed: C26.2, R61.1, R65.1, U8.4 (FB)
unnamed: D18.1, L5.1, U8.2 (OUT)
unnamed: C30.1, C31.1, R68.2, U8.1 (VIN)
unnamed: R75.1, U9.6 (GATE)
unnamed: R77.2, R78.1, U9.7 (OV)
unnamed: C38.2, U9.4 (VCAP)
unnamed: C43.1, U10.13 (TC)
unnamed: C44.1, U11.13 (TC)
unnamed: R81.2, R86.2, U12.3 (+)
unnamed: R83.2, R87.1, U12.2 (-)
unnamed: R89.2, R93.2, U12.5 (+)
unnamed: R91.2, R94.1, U12.6 (-)
unnamed: C42.2, R80.1, TP7.1 (1_1), U13.3 (IN+)
unnamed: C42.1, R84.2, U13.2 (IN-)
unnamed: C50.2, R95.2, TP9.1 (1_1), U13.5 (IN+)
unnamed: C50.1, R90.2, U13.6 (IN-)
unnamed: R82.1, U14.6 (GATE)
unnamed: R85.2, R88.1, U14.7 (OV)
unnamed: C45.2, U14.4 (VCAP)
unnamed: R92.1, U15.6 (GATE)
unnamed: R96.2, R97.1, U15.7 (OV)
unnamed: C51.2, U15.4 (VCAP)
unnamed: R98.1, U16.6 (GATE)
unnamed: R99.2, R100.1, U16.7 (OV)
unnamed: C53.2, U16.4 (VCAP)
Ref_3.3V: C14.1, D8.3 (K), R32.2
Ref_5V: C2.1, D1.3 (K), R3.2
SRC 3.3_HIGH: D9.1 (anode), Q7.1 (S), Q7.2 (S), Q7.3 (S), Q8.1 (S), Q8.2 (S), Q8.3 (S), R36.1, U15.8 (SRC)
SRC 3.3_LOW: D13.1 (anode), Q10.1 (S), Q10.2 (S), Q10.3 (S), Q11.1 (S), Q11.2 (S), Q11.3 (S), R49.1, U16.8 (SRC)
SRC 5_HIGH: D2.1 (anode), Q1.1 (S), Q1.2 (S), Q1.3 (S), Q2.1 (S), Q2.2 (S), Q2.3 (S), R9.1, U9.8 (SRC)
SRC 5_LOW: D6.1 (anode), Q4.1 (S), Q4.2 (S), Q4.3 (S), Q5.1 (S), Q5.2 (S), Q5.3 (S), R22.1, U14.8 (SRC)
VSENSE_3V3+: R27.1, R40.2, R41.2, U3.3
VSENSE_5V+: R6.1, R12.2, R15.2, U1.3
V_out +3V3: D12.2, J2.2, L4.2, R41.1
V_out +5V: D4.2, J1.2, L1.2, R12.1

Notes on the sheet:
Voltage Measuring
3100 = 5.04V
Power IN
Control Voltage Converter
Channel 2 Remote Sensing Network
3.3 Volt Converter
Channel 2 3.3 volts
5 Volt Converter
1.6mv/ohm
Decoupling
1.680k = 3.3V 1.9mv/ohm
Channel 1 5 volts
Channel 1 Remote Sensing Network
